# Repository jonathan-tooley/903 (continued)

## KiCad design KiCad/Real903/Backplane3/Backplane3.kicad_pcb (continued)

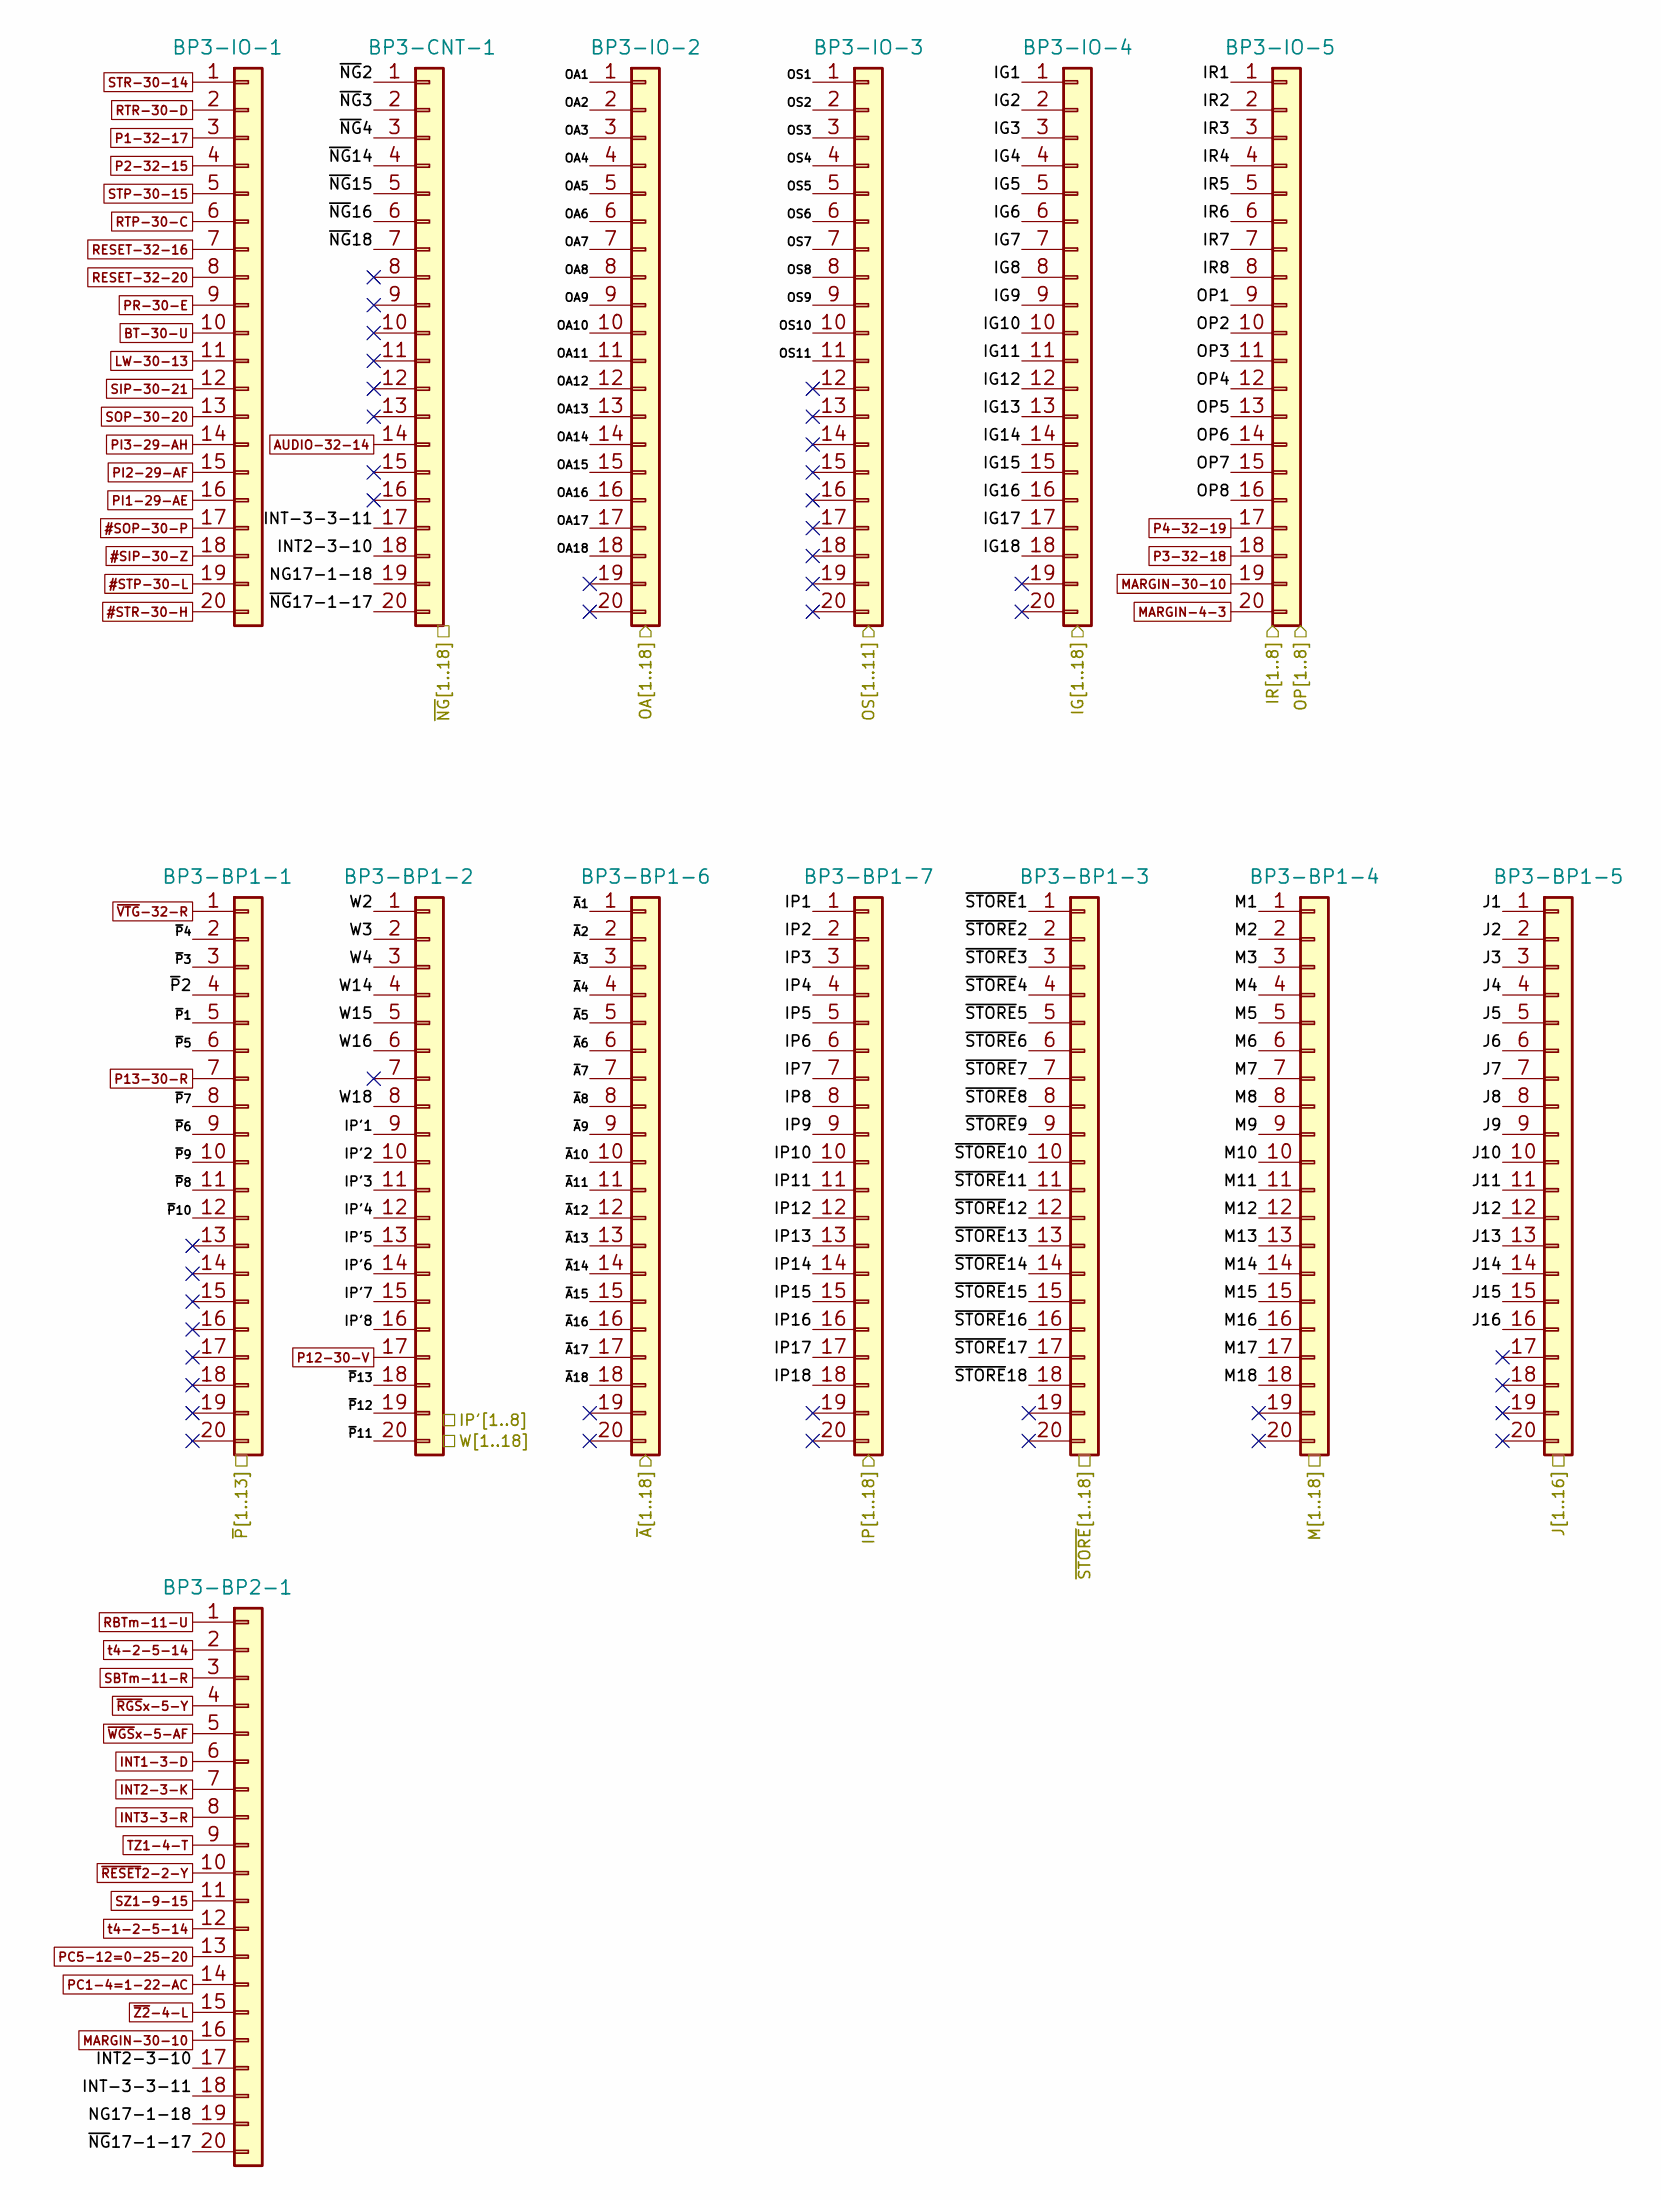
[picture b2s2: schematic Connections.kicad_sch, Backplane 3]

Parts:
BP3-BP1-1, BP3-BP1-2, BP3-BP1-3, BP3-BP1-4, BP3-BP1-5, BP3-BP1-6, BP3-BP1-7, BP3-BP2-1, BP3-CNT-1, BP3-IO-1, BP3-IO-2, BP3-IO-3, BP3-IO-4, BP3-IO-5: IDC-Header_2x10_P2.54mm_Latch_Vertical

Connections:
#SIP-30-Z: BP3-IO-1.18; also elsewhere on the board
#SOP-30-P: BP3-IO-1.17; also elsewhere on the board
#STP-30-L: BP3-IO-1.19; also elsewhere on the board
#STR-30-H: BP3-IO-1.20; also elsewhere on the board
/Connections/IG1: BP3-IO-4.1; also elsewhere on the board
/Connections/IG2: BP3-IO-4.2; also elsewhere on the board
/Connections/IG3: BP3-IO-4.3; also elsewhere on the board
/Connections/IG4: BP3-IO-4.4; also elsewhere on the board
/Connections/IG5: BP3-IO-4.5; also elsewhere on the board
/Connections/IG6: BP3-IO-4.6; also elsewhere on the board
/Connections/IG7: BP3-IO-4.7; also elsewhere on the board
/Connections/IG8: BP3-IO-4.8; also elsewhere on the board
/Connections/IG9: BP3-IO-4.9; also elsewhere on the board
/Connections/IG10: BP3-IO-4.10; also elsewhere on the board
/Connections/IG11: BP3-IO-4.11; also elsewhere on the board
/Connections/IG12: BP3-IO-4.12; also elsewhere on the board
/Connections/IG13: BP3-IO-4.13; also elsewhere on the board
/Connections/IG14: BP3-IO-4.14; also elsewhere on the board
/Connections/IG15: BP3-IO-4.15; also elsewhere on the board
/Connections/IG16: BP3-IO-4.16; also elsewhere on the board
/Connections/IG17: BP3-IO-4.17; also elsewhere on the board
/Connections/IG18: BP3-IO-4.18; also elsewhere on the board
/Connections/INT2-3-10: BP3-BP2-1.17, BP3-CNT-1.18
/Connections/INT-3-3-11: BP3-BP2-1.18, BP3-CNT-1.17
/Connections/IP1: BP3-BP1-7.1; also elsewhere on the board
/Connections/IP2: BP3-BP1-7.2; also elsewhere on the board
/Connections/IP3: BP3-BP1-7.3; also elsewhere on the board
/Connections/IP4: BP3-BP1-7.4; also elsewhere on the board
/Connections/IP5: BP3-BP1-7.5; also elsewhere on the board
/Connections/IP6: BP3-BP1-7.6; also elsewhere on the board
/Connections/IP7: BP3-BP1-7.7; also elsewhere on the board
/Connections/IP8: BP3-BP1-7.8; also elsewhere on the board
/Connections/IP9: BP3-BP1-7.9; also elsewhere on the board
/Connections/IP10: BP3-BP1-7.10; also elsewhere on the board
/Connections/IP11: BP3-BP1-7.11; also elsewhere on the board
/Connections/IP12: BP3-BP1-7.12; also elsewhere on the board
/Connections/IP13: BP3-BP1-7.13; also elsewhere on the board
/Connections/IP14: BP3-BP1-7.14; also elsewhere on the board
/Connections/IP15: BP3-BP1-7.15; also elsewhere on the board
/Connections/IP16: BP3-BP1-7.16; also elsewhere on the board
/Connections/IP17: BP3-BP1-7.17; also elsewhere on the board
/Connections/IP18: BP3-BP1-7.18; also elsewhere on the board
/Connections/IP'1: BP3-BP1-2.9; also elsewhere on the board
/Connections/IP'2: BP3-BP1-2.10; also elsewhere on the board
/Connections/IP'3: BP3-BP1-2.11; also elsewhere on the board
/Connections/IP'4: BP3-BP1-2.12; also elsewhere on the board
/Connections/IP'5: BP3-BP1-2.13; also elsewhere on the board
/Connections/IP'6: BP3-BP1-2.14; also elsewhere on the board
/Connections/IP'7: BP3-BP1-2.15; also elsewhere on the board
/Connections/IP'8: BP3-BP1-2.16; also elsewhere on the board
/Connections/IR1: BP3-IO-5.1; also elsewhere on the board
/Connections/IR2: BP3-IO-5.2; also elsewhere on the board
/Connections/IR3: BP3-IO-5.3; also elsewhere on the board
/Connections/IR4: BP3-IO-5.4; also elsewhere on the board
/Connections/IR5: BP3-IO-5.5; also elsewhere on the board
/Connections/IR6: BP3-IO-5.6; also elsewhere on the board
/Connections/IR7: BP3-IO-5.7; also elsewhere on the board
/Connections/IR8: BP3-IO-5.8; also elsewhere on the board
/Connections/J1: BP3-BP1-5.1; also elsewhere on the board
/Connections/J2: BP3-BP1-5.2; also elsewhere on the board
/Connections/J3: BP3-BP1-5.3; also elsewhere on the board
/Connections/J4: BP3-BP1-5.4; also elsewhere on the board
/Connections/J5: BP3-BP1-5.5; also elsewhere on the board
/Connections/J6: BP3-BP1-5.6; also elsewhere on the board
/Connections/J7: BP3-BP1-5.7; also elsewhere on the board
/Connections/J8: BP3-BP1-5.8; also elsewhere on the board
/Connections/J9: BP3-BP1-5.9; also elsewhere on the board
/Connections/J10: BP3-BP1-5.10; also elsewhere on the board
/Connections/J11: BP3-BP1-5.11; also elsewhere on the board
/Connections/J12: BP3-BP1-5.12; also elsewhere on the board
/Connections/J13: BP3-BP1-5.13; also elsewhere on the board
/Connections/J14: BP3-BP1-5.14; also elsewhere on the board
/Connections/J15: BP3-BP1-5.15; also elsewhere on the board
/Connections/J16: BP3-BP1-5.16; also elsewhere on the board
/Connections/M1: BP3-BP1-4.1; also elsewhere on the board
/Connections/M2: BP3-BP1-4.2; also elsewhere on the board
/Connections/M3: BP3-BP1-4.3; also elsewhere on the board
/Connections/M4: BP3-BP1-4.4; also elsewhere on the board
/Connections/M5: BP3-BP1-4.5; also elsewhere on the board
/Connections/M6: BP3-BP1-4.6; also elsewhere on the board
/Connections/M7: BP3-BP1-4.7; also elsewhere on the board
/Connections/M8: BP3-BP1-4.8; also elsewhere on the board
/Connections/M9: BP3-BP1-4.9; also elsewhere on the board
/Connections/M10: BP3-BP1-4.10; also elsewhere on the board
/Connections/M11: BP3-BP1-4.11; also elsewhere on the board
/Connections/M12: BP3-BP1-4.12; also elsewhere on the board
/Connections/M13: BP3-BP1-4.13; also elsewhere on the board
/Connections/M14: BP3-BP1-4.14; also elsewhere on the board
/Connections/M15: BP3-BP1-4.15; also elsewhere on the board
/Connections/M16: BP3-BP1-4.16; also elsewhere on the board
/Connections/M17: BP3-BP1-4.17; also elsewhere on the board
/Connections/M18: BP3-BP1-4.18; also elsewhere on the board
/Connections/NG17-1-18: BP3-BP2-1.19, BP3-CNT-1.19
/Connections/OA1: BP3-IO-2.1; also elsewhere on the board
/Connections/OA2: BP3-IO-2.2; also elsewhere on the board
/Connections/OA3: BP3-IO-2.3; also elsewhere on the board
/Connections/OA4: BP3-IO-2.4; also elsewhere on the board
/Connections/OA5: BP3-IO-2.5; also elsewhere on the board
/Connections/OA6: BP3-IO-2.6; also elsewhere on the board
/Connections/OA7: BP3-IO-2.7; also elsewhere on the board
/Connections/OA8: BP3-IO-2.8; also elsewhere on the board
/Connections/OA9: BP3-IO-2.9; also elsewhere on the board
/Connections/OA10: BP3-IO-2.10; also elsewhere on the board
/Connections/OA11: BP3-IO-2.11; also elsewhere on the board
/Connections/OA12: BP3-IO-2.12; also elsewhere on the board
/Connections/OA13: BP3-IO-2.13; also elsewhere on the board
/Connections/OA14: BP3-IO-2.14; also elsewhere on the board
/Connections/OA15: BP3-IO-2.15; also elsewhere on the board
/Connections/OA16: BP3-IO-2.16; also elsewhere on the board
/Connections/OA17: BP3-IO-2.17; also elsewhere on the board
/Connections/OA18: BP3-IO-2.18; also elsewhere on the board
/Connections/OP1: BP3-IO-5.9; also elsewhere on the board
/Connections/OP2: BP3-IO-5.10; also elsewhere on the board
/Connections/OP3: BP3-IO-5.11; also elsewhere on the board
/Connections/OP4: BP3-IO-5.12; also elsewhere on the board
/Connections/OP5: BP3-IO-5.13; also elsewhere on the board
/Connections/OP6: BP3-IO-5.14; also elsewhere on the board
/Connections/OP7: BP3-IO-5.15; also elsewhere on the board
/Connections/OP8: BP3-IO-5.16; also elsewhere on the board
/Connections/OS1: BP3-IO-3.1; also elsewhere on the board
/Connections/OS2: BP3-IO-3.2; also elsewhere on the board
/Connections/OS3: BP3-IO-3.3; also elsewhere on the board
/Connections/OS4: BP3-IO-3.4; also elsewhere on the board
/Connections/OS5: BP3-IO-3.5; also elsewhere on the board
/Connections/OS6: BP3-IO-3.6; also elsewhere on the board
/Connections/OS7: BP3-IO-3.7; also elsewhere on the board
/Connections/OS8: BP3-IO-3.8; also elsewhere on the board
/Connections/OS9: BP3-IO-3.9; also elsewhere on the board
/Connections/OS10: BP3-IO-3.10; also elsewhere on the board
/Connections/OS11: BP3-IO-3.11; also elsewhere on the board
/Connections/W2: BP3-BP1-2.1; also elsewhere on the board
/Connections/W3: BP3-BP1-2.2; also elsewhere on the board
/Connections/W4: BP3-BP1-2.3; also elsewhere on the board
/Connections/W14: BP3-BP1-2.4; also elsewhere on the board
/Connections/W15: BP3-BP1-2.5; also elsewhere on the board
/Connections/W16: BP3-BP1-2.6; also elsewhere on the board
/Connections/W18: BP3-BP1-2.8; also elsewhere on the board
/Connections/~A1: BP3-BP1-6.1; also elsewhere on the board
/Connections/~A2: BP3-BP1-6.2; also elsewhere on the board
/Connections/~A3: BP3-BP1-6.3; also elsewhere on the board
/Connections/~A4: BP3-BP1-6.4; also elsewhere on the board
/Connections/~A5: BP3-BP1-6.5; also elsewhere on the board
/Connections/~A6: BP3-BP1-6.6; also elsewhere on the board
/Connections/~A7: BP3-BP1-6.7; also elsewhere on the board
/Connections/~A8: BP3-BP1-6.8; also elsewhere on the board
/Connections/~A9: BP3-BP1-6.9; also elsewhere on the board
/Connections/~A10: BP3-BP1-6.10; also elsewhere on the board
/Connections/~A11: BP3-BP1-6.11; also elsewhere on the board
/Connections/~A12: BP3-BP1-6.12; also elsewhere on the board
/Connections/~A13: BP3-BP1-6.13; also elsewhere on the board
/Connections/~A14: BP3-BP1-6.14; also elsewhere on the board
/Connections/~A15: BP3-BP1-6.15; also elsewhere on the board
/Connections/~A16: BP3-BP1-6.16; also elsewhere on the board
/Connections/~A17: BP3-BP1-6.17; also elsewhere on the board
/Connections/~A18: BP3-BP1-6.18; also elsewhere on the board
/Connections/~NG2: BP3-CNT-1.1; also elsewhere on the board
/Connections/~NG3: BP3-CNT-1.2; also elsewhere on the board
/Connections/~NG4: BP3-CNT-1.3; also elsewhere on the board
/Connections/~NG14: BP3-CNT-1.4; also elsewhere on the board
/Connections/~NG15: BP3-CNT-1.5; also elsewhere on the board
/Connections/~NG16: BP3-CNT-1.6; also elsewhere on the board
/Connections/~NG17-1-17: BP3-BP2-1.20, BP3-CNT-1.20
/Connections/~NG18: BP3-CNT-1.7; also elsewhere on the board
/Connections/~P1: BP3-BP1-1.5; also elsewhere on the board
/Connections/~P2: BP3-BP1-1.4; also elsewhere on the board
/Connections/~P3: BP3-BP1-1.3; also elsewhere on the board
/Connections/~P4: BP3-BP1-1.2; also elsewhere on the board
/Connections/~P5: BP3-BP1-1.6; also elsewhere on the board
/Connections/~P6: BP3-BP1-1.9; also elsewhere on the board
/Connections/~P7: BP3-BP1-1.8; also elsewhere on the board
/Connections/~P8: BP3-BP1-1.11; also elsewhere on the board
/Connections/~P9: BP3-BP1-1.10; also elsewhere on the board
/Connections/~P10: BP3-BP1-1.12; also elsewhere on the board
/Connections/~P11: BP3-BP1-2.20; also elsewhere on the board
/Connections/~P12: BP3-BP1-2.19; also elsewhere on the board
/Connections/~P13: BP3-BP1-2.18; also elsewhere on the board
/Connections/~STORE1: BP3-BP1-3.1; also elsewhere on the board
/Connections/~STORE2: BP3-BP1-3.2; also elsewhere on the board
/Connections/~STORE3: BP3-BP1-3.3; also elsewhere on the board
/Connections/~STORE4: BP3-BP1-3.4; also elsewhere on the board
/Connections/~STORE5: BP3-BP1-3.5; also elsewhere on the board
/Connections/~STORE6: BP3-BP1-3.6; also elsewhere on the board
/Connections/~STORE7: BP3-BP1-3.7; also elsewhere on the board
/Connections/~STORE8: BP3-BP1-3.8; also elsewhere on the board
/Connections/~STORE9: BP3-BP1-3.9; also elsewhere on the board
/Connections/~STORE10: BP3-BP1-3.10; also elsewhere on the board
/Connections/~STORE11: BP3-BP1-3.11; also elsewhere on the board
/Connections/~STORE12: BP3-BP1-3.12; also elsewhere on the board
/Connections/~STORE13: BP3-BP1-3.13; also elsewhere on the board
/Connections/~STORE14: BP3-BP1-3.14; also elsewhere on the board
/Connections/~STORE15: BP3-BP1-3.15; also elsewhere on the board
/Connections/~STORE16: BP3-BP1-3.16; also elsewhere on the board
/Connections/~STORE17: BP3-BP1-3.17; also elsewhere on the board
/Connections/~STORE18: BP3-BP1-3.18; also elsewhere on the board
AUDIO-32-14: BP3-CNT-1.14; also elsewhere on the board
BT-30-U: BP3-IO-1.10; also elsewhere on the board
INT1-3-D: BP3-BP2-1.6; also elsewhere on the board
INT2-3-K: BP3-BP2-1.7; also elsewhere on the board
INT3-3-R: BP3-BP2-1.8; also elsewhere on the board
LW-30-13: BP3-IO-1.11; also elsewhere on the board
MARGIN-4-3: BP3-IO-5.20
MARGIN-30-10: BP3-BP2-1.16, BP3-IO-5.19; also elsewhere on the board
P1-32-17: BP3-IO-1.3; also elsewhere on the board
P2-32-15: BP3-IO-1.4; also elsewhere on the board
P3-32-18: BP3-IO-5.18; also elsewhere on the board
P4-32-19: BP3-IO-5.17; also elsewhere on the board
P12-30-V: BP3-BP1-2.17; also elsewhere on the board
P13-30-R: BP3-BP1-1.7; also elsewhere on the board
PC1-4=1-22-AC: BP3-BP2-1.14; also elsewhere on the board
PC5-12=0-25-20: BP3-BP2-1.13; also elsewhere on the board
PI1-29-AE: BP3-IO-1.16; also elsewhere on the board
PI2-29-AF: BP3-IO-1.15; also elsewhere on the board
PI3-29-AH: BP3-IO-1.14; also elsewhere on the board
PR-30-E: BP3-IO-1.9; also elsewhere on the board
RBTm-11-U: BP3-BP2-1.1; also elsewhere on the board
RESET-32-16: BP3-IO-1.7; also elsewhere on the board
RESET-32-20: BP3-IO-1.8; also elsewhere on the board
RTP-30-C: BP3-IO-1.6; also elsewhere on the board
RTR-30-D: BP3-IO-1.2; also elsewhere on the board
SBTm-11-R: BP3-BP2-1.3; also elsewhere on the board
SIP-30-21: BP3-IO-1.12; also elsewhere on the board
SOP-30-20: BP3-IO-1.13; also elsewhere on the board
STP-30-15: BP3-IO-1.5; also elsewhere on the board
STR-30-14: BP3-IO-1.1; also elsewhere on the board
SZ1-9-15: BP3-BP2-1.11; also elsewhere on the board
TZ1-4-T: BP3-BP2-1.9; also elsewhere on the board
t4-2-5-14: BP3-BP2-1.2, BP3-BP2-1.12; also elsewhere on the board
~RESET2-2-Y: BP3-BP2-1.10; also elsewhere on the board
~RGSx-5-Y: BP3-BP2-1.4; also elsewhere on the board
~VTG-32-R: BP3-BP1-1.1; also elsewhere on the board
~WGSx-5-AF: BP3-BP2-1.5; also elsewhere on the board
~Z2-4-L: BP3-BP2-1.15; also elsewhere on the board

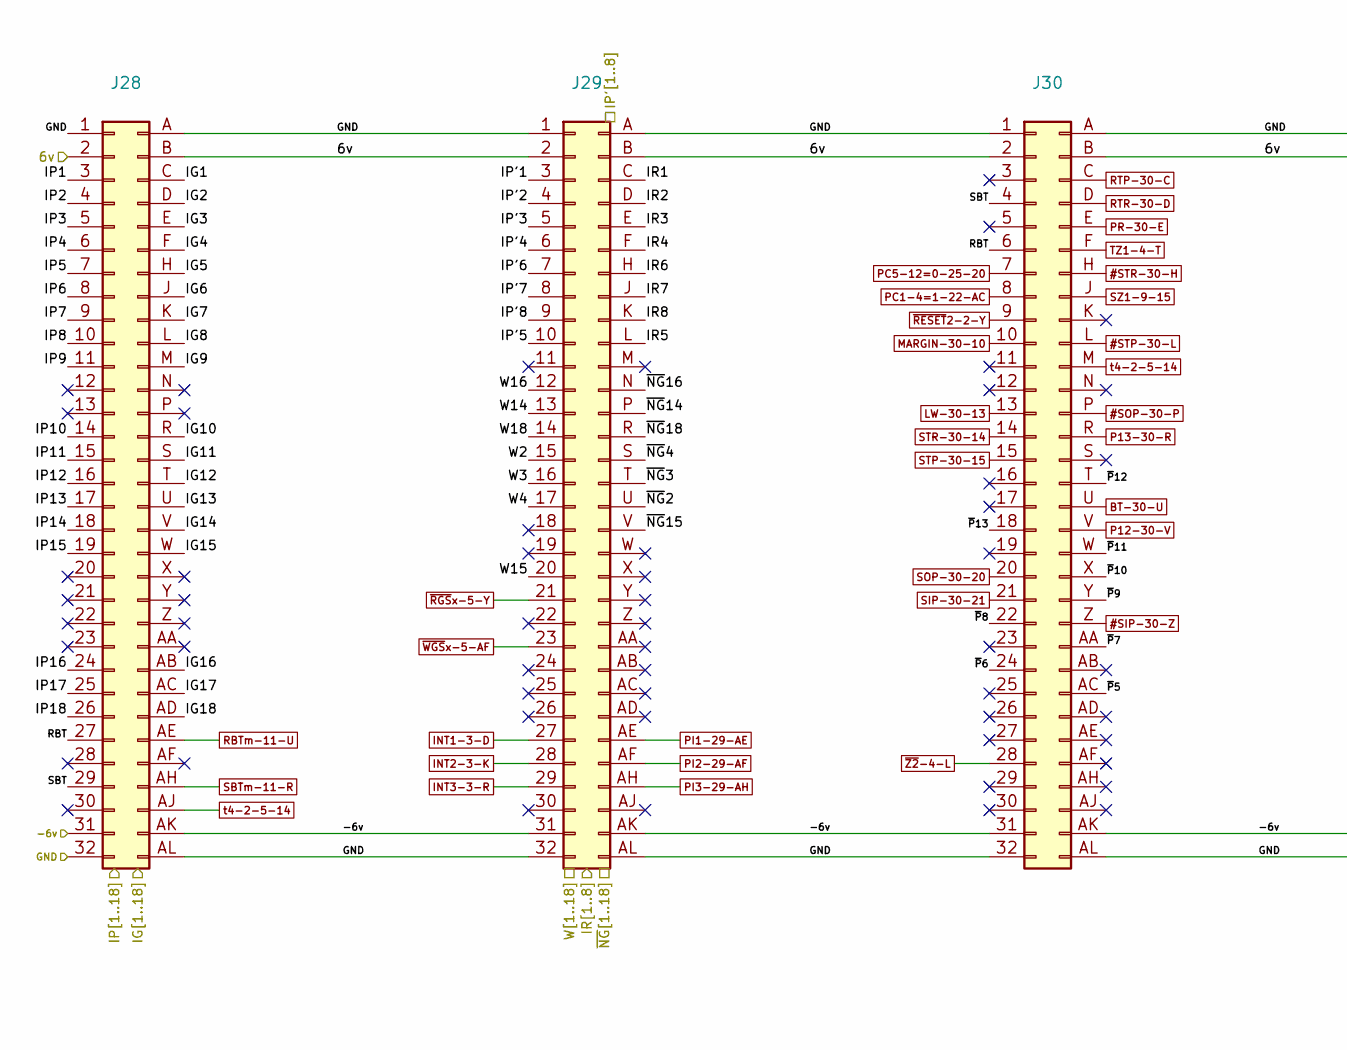
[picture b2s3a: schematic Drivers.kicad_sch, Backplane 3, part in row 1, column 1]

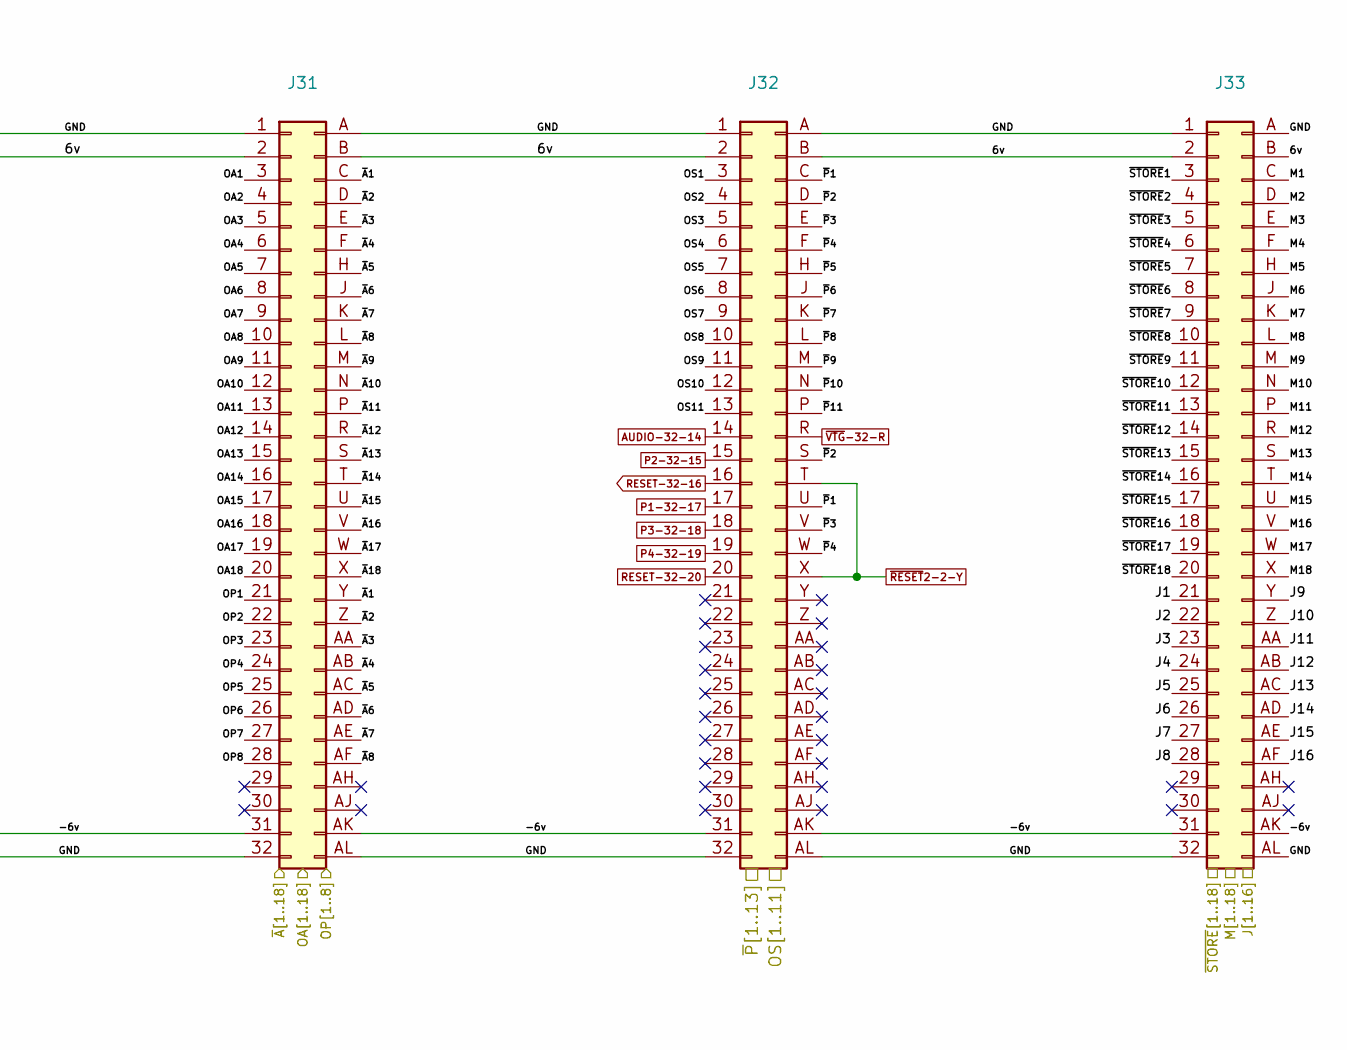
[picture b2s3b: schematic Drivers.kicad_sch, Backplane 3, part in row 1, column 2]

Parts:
J28, J29, J30, J31, J32, J33: DIN41612_B_2x32_Vertical

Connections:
6v: J28.2, J28.B, J29.2, J29.B, J30.2, J30.B, J31.2, J31.B, J32.2, J32.B, J33.2, J33.B; also elsewhere on the board
#SIP-30-Z: J30.Z; also elsewhere on the board
#SOP-30-P: J30.P; also elsewhere on the board
#STP-30-L: J30.L; also elsewhere on the board
#STR-30-H: J30.H; also elsewhere on the board
/Connections/IG1: J28.C; also elsewhere on the board
/Connections/IG2: J28.D; also elsewhere on the board
/Connections/IG3: J28.E; also elsewhere on the board
/Connections/IG4: J28.F; also elsewhere on the board
/Connections/IG5: J28.H; also elsewhere on the board
/Connections/IG6: J28.J; also elsewhere on the board
/Connections/IG7: J28.K; also elsewhere on the board
/Connections/IG8: J28.L; also elsewhere on the board
/Connections/IG9: J28.M; also elsewhere on the board
/Connections/IG10: J28.R; also elsewhere on the board
/Connections/IG11: J28.S; also elsewhere on the board
/Connections/IG12: J28.T; also elsewhere on the board
/Connections/IG13: J28.U; also elsewhere on the board
/Connections/IG14: J28.V; also elsewhere on the board
/Connections/IG15: J28.W; also elsewhere on the board
/Connections/IG16: J28.AB; also elsewhere on the board
/Connections/IG17: J28.AC; also elsewhere on the board
/Connections/IG18: J28.AD; also elsewhere on the board
/Connections/IP1: J28.3; also elsewhere on the board
/Connections/IP2: J28.4; also elsewhere on the board
/Connections/IP3: J28.5; also elsewhere on the board
/Connections/IP4: J28.6; also elsewhere on the board
/Connections/IP5: J28.7; also elsewhere on the board
/Connections/IP6: J28.8; also elsewhere on the board
/Connections/IP7: J28.9; also elsewhere on the board
/Connections/IP8: J28.10; also elsewhere on the board
/Connections/IP9: J28.11; also elsewhere on the board
/Connections/IP10: J28.14; also elsewhere on the board
/Connections/IP11: J28.15; also elsewhere on the board
/Connections/IP12: J28.16; also elsewhere on the board
/Connections/IP13: J28.17; also elsewhere on the board
/Connections/IP14: J28.18; also elsewhere on the board
/Connections/IP15: J28.19; also elsewhere on the board
/Connections/IP16: J28.24; also elsewhere on the board
/Connections/IP17: J28.25; also elsewhere on the board
/Connections/IP18: J28.26; also elsewhere on the board
/Connections/IP'1: J29.3; also elsewhere on the board
/Connections/IP'2: J29.4; also elsewhere on the board
/Connections/IP'3: J29.5; also elsewhere on the board
/Connections/IP'4: J29.6; also elsewhere on the board
/Connections/IP'5: J29.10; also elsewhere on the board
/Connections/IP'6: J29.7; also elsewhere on the board
/Connections/IP'7: J29.8; also elsewhere on the board
/Connections/IP'8: J29.9; also elsewhere on the board
/Connections/IR1: J29.C; also elsewhere on the board
/Connections/IR2: J29.D; also elsewhere on the board
/Connections/IR3: J29.E; also elsewhere on the board
/Connections/IR4: J29.F; also elsewhere on the board
/Connections/IR5: J29.L; also elsewhere on the board
/Connections/IR6: J29.H; also elsewhere on the board
/Connections/IR7: J29.J; also elsewhere on the board
/Connections/IR8: J29.K; also elsewhere on the board
/Connections/J1: J33.21; also elsewhere on the board
/Connections/J2: J33.22; also elsewhere on the board
/Connections/J3: J33.23; also elsewhere on the board
/Connections/J4: J33.24; also elsewhere on the board
/Connections/J5: J33.25; also elsewhere on the board
/Connections/J6: J33.26; also elsewhere on the board
/Connections/J7: J33.27; also elsewhere on the board
/Connections/J8: J33.28; also elsewhere on the board
/Connections/J9: J33.Y; also elsewhere on the board
/Connections/J10: J33.Z; also elsewhere on the board
/Connections/J11: J33.AA; also elsewhere on the board
/Connections/J12: J33.AB; also elsewhere on the board
/Connections/J13: J33.AC; also elsewhere on the board
/Connections/J14: J33.AD; also elsewhere on the board
/Connections/J15: J33.AE; also elsewhere on the board
/Connections/J16: J33.AF; also elsewhere on the board
/Connections/M1: J33.C; also elsewhere on the board
/Connections/M2: J33.D; also elsewhere on the board
/Connections/M3: J33.E; also elsewhere on the board
/Connections/M4: J33.F; also elsewhere on the board
/Connections/M5: J33.H; also elsewhere on the board
/Connections/M6: J33.J; also elsewhere on the board
/Connections/M7: J33.K; also elsewhere on the board
/Connections/M8: J33.L; also elsewhere on the board
/Connections/M9: J33.M; also elsewhere on the board
/Connections/M10: J33.N; also elsewhere on the board
/Connections/M11: J33.P; also elsewhere on the board
/Connections/M12: J33.R; also elsewhere on the board
/Connections/M13: J33.S; also elsewhere on the board
/Connections/M14: J33.T; also elsewhere on the board
/Connections/M15: J33.U; also elsewhere on the board
/Connections/M16: J33.V; also elsewhere on the board
/Connections/M17: J33.W; also elsewhere on the board
/Connections/M18: J33.X; also elsewhere on the board
/Connections/OA1: J31.3; also elsewhere on the board
/Connections/OA2: J31.4; also elsewhere on the board
/Connections/OA3: J31.5; also elsewhere on the board
/Connections/OA4: J31.6; also elsewhere on the board
/Connections/OA5: J31.7; also elsewhere on the board
/Connections/OA6: J31.8; also elsewhere on the board
/Connections/OA7: J31.9; also elsewhere on the board
/Connections/OA8: J31.10; also elsewhere on the board
/Connections/OA9: J31.11; also elsewhere on the board
/Connections/OA10: J31.12; also elsewhere on the board
/Connections/OA11: J31.13; also elsewhere on the board
/Connections/OA12: J31.14; also elsewhere on the board
/Connections/OA13: J31.15; also elsewhere on the board
/Connections/OA14: J31.16; also elsewhere on the board
/Connections/OA15: J31.17; also elsewhere on the board
/Connections/OA16: J31.18; also elsewhere on the board
/Connections/OA17: J31.19; also elsewhere on the board
/Connections/OA18: J31.20; also elsewhere on the board
/Connections/OP1: J31.21; also elsewhere on the board
/Connections/OP2: J31.22; also elsewhere on the board
/Connections/OP3: J31.23; also elsewhere on the board
/Connections/OP4: J31.24; also elsewhere on the board
/Connections/OP5: J31.25; also elsewhere on the board
/Connections/OP6: J31.26; also elsewhere on the board
/Connections/OP7: J31.27; also elsewhere on the board
/Connections/OP8: J31.28; also elsewhere on the board
/Connections/OS1: J32.3; also elsewhere on the board
/Connections/OS2: J32.4; also elsewhere on the board
/Connections/OS3: J32.5; also elsewhere on the board
/Connections/OS4: J32.6; also elsewhere on the board
/Connections/OS5: J32.7; also elsewhere on the board
/Connections/OS6: J32.8; also elsewhere on the board
/Connections/OS7: J32.9; also elsewhere on the board
/Connections/OS8: J32.10; also elsewhere on the board
/Connections/OS9: J32.11; also elsewhere on the board
/Connections/OS10: J32.12; also elsewhere on the board
/Connections/OS11: J32.13; also elsewhere on the board
/Connections/W2: J29.15; also elsewhere on the board
/Connections/W3: J29.16; also elsewhere on the board
/Connections/W4: J29.17; also elsewhere on the board
/Connections/W14: J29.13; also elsewhere on the board
/Connections/W15: J29.20; also elsewhere on the board
/Connections/W16: J29.12; also elsewhere on the board
/Connections/W18: J29.14; also elsewhere on the board
/Connections/~A1: J31.C, J31.Y; also elsewhere on the board
/Connections/~A2: J31.D, J31.Z; also elsewhere on the board
/Connections/~A3: J31.AA, J31.E; also elsewhere on the board
/Connections/~A4: J31.AB, J31.F; also elsewhere on the board
/Connections/~A5: J31.AC, J31.H; also elsewhere on the board
/Connections/~A6: J31.AD, J31.J; also elsewhere on the board
/Connections/~A7: J31.AE, J31.K; also elsewhere on the board
/Connections/~A8: J31.AF, J31.L; also elsewhere on the board
/Connections/~A9: J31.M; also elsewhere on the board
/Connections/~A10: J31.N; also elsewhere on the board
/Connections/~A11: J31.P; also elsewhere on the board
/Connections/~A12: J31.R; also elsewhere on the board
/Connections/~A13: J31.S; also elsewhere on the board
/Connections/~A14: J31.T; also elsewhere on the board
/Connections/~A15: J31.U; also elsewhere on the board
/Connections/~A16: J31.V; also elsewhere on the board
/Connections/~A17: J31.W; also elsewhere on the board
/Connections/~A18: J31.X; also elsewhere on the board
/Connections/~NG2: J29.U; also elsewhere on the board
/Connections/~NG3: J29.T; also elsewhere on the board
/Connections/~NG4: J29.S; also elsewhere on the board
/Connections/~NG14: J29.P; also elsewhere on the board
/Connections/~NG15: J29.V; also elsewhere on the board
/Connections/~NG16: J29.N; also elsewhere on the board
/Connections/~NG18: J29.R; also elsewhere on the board
/Connections/~P1: J32.C, J32.U; also elsewhere on the board
/Connections/~P2: J32.D, J32.S; also elsewhere on the board
/Connections/~P3: J32.E, J32.V; also elsewhere on the board
/Connections/~P4: J32.F, J32.W; also elsewhere on the board
/Connections/~P5: J30.AC, J32.H; also elsewhere on the board
/Connections/~P6: J30.24, J32.J; also elsewhere on the board
/Connections/~P7: J30.AA, J32.K; also elsewhere on the board
/Connections/~P8: J30.22, J32.L; also elsewhere on the board
/Connections/~P9: J30.Y, J32.M; also elsewhere on the board
/Connections/~P10: J30.X, J32.N; also elsewhere on the board
/Connections/~P11: J30.W, J32.P; also elsewhere on the board
/Connections/~P12: J30.T; also elsewhere on the board
/Connections/~P13: J30.18; also elsewhere on the board
/Connections/~STORE1: J33.3; also elsewhere on the board
/Connections/~STORE2: J33.4; also elsewhere on the board
/Connections/~STORE3: J33.5; also elsewhere on the board
/Connections/~STORE4: J33.6; also elsewhere on the board
/Connections/~STORE5: J33.7; also elsewhere on the board
/Connections/~STORE6: J33.8; also elsewhere on the board
/Connections/~STORE7: J33.9; also elsewhere on the board
/Connections/~STORE8: J33.10; also elsewhere on the board
/Connections/~STORE9: J33.11; also elsewhere on the board
/Connections/~STORE10: J33.12; also elsewhere on the board
/Connections/~STORE11: J33.13; also elsewhere on the board
/Connections/~STORE12: J33.14; also elsewhere on the board
/Connections/~STORE13: J33.15; also elsewhere on the board
/Connections/~STORE14: J33.16; also elsewhere on the board
/Connections/~STORE15: J33.17; also elsewhere on the board
/Connections/~STORE16: J33.18; also elsewhere on the board
/Connections/~STORE17: J33.19; also elsewhere on the board
/Connections/~STORE18: J33.20; also elsewhere on the board
/Drivers/RBT: J28.27, J30.6
/Drivers/SBT: J28.29, J30.4
AUDIO-32-14: J32.14; also elsewhere on the board
BT-30-U: J30.U; also elsewhere on the board
GND: J28.1, J28.32, J28.A, J28.AL, J29.1, J29.32, J29.A, J29.AL, J30.1, J30.32, J30.A, J30.AL, J31.1, J31.32, J31.A, J31.AL, J32.1, J32.32, J32.A, J32.AL, J33.1, J33.32, J33.A, J33.AL; also elsewhere on the board
INT1-3-D: J29.27; also elsewhere on the board
INT2-3-K: J29.28; also elsewhere on the board
INT3-3-R: J29.29; also elsewhere on the board
LW-30-13: J30.13; also elsewhere on the board
MARGIN-30-10: J30.10; also elsewhere on the board
Neg6v: J28.31, J28.AK, J29.31, J29.AK, J30.31, J30.AK, J31.31, J31.AK, J32.31, J32.AK, J33.31, J33.AK; also elsewhere on the board
P1-32-17: J32.17; also elsewhere on the board
P2-32-15: J32.15; also elsewhere on the board
P3-32-18: J32.18; also elsewhere on the board
P4-32-19: J32.19; also elsewhere on the board
P12-30-V: J30.V; also elsewhere on the board
P13-30-R: J30.R; also elsewhere on the board
PC1-4=1-22-AC: J30.8; also elsewhere on the board
PC5-12=0-25-20: J30.7; also elsewhere on the board
PI1-29-AE: J29.AE; also elsewhere on the board
PI2-29-AF: J29.AF; also elsewhere on the board
PI3-29-AH: J29.AH; also elsewhere on the board
PR-30-E: J30.E; also elsewhere on the board
RBTm-11-U: J28.AE; also elsewhere on the board
RESET-32-16: J32.16; also elsewhere on the board
RESET-32-20: J32.20; also elsewhere on the board
RTP-30-C: J30.C; also elsewhere on the board
RTR-30-D: J30.D; also elsewhere on the board
SBTm-11-R: J28.AH; also elsewhere on the board
SIP-30-21: J30.21; also elsewhere on the board
SOP-30-20: J30.20; also elsewhere on the board
STP-30-15: J30.15; also elsewhere on the board
STR-30-14: J30.14; also elsewhere on the board
SZ1-9-15: J30.J; also elsewhere on the board
TZ1-4-T: J30.F; also elsewhere on the board
t4-2-5-14: J28.AJ, J30.M; also elsewhere on the board
~RESET2-2-Y: J30.9, J32.T, J32.X; also elsewhere on the board
~RGSx-5-Y: J29.21; also elsewhere on the board
~VTG-32-R: J32.R; also elsewhere on the board
~WGSx-5-AF: J29.23; also elsewhere on the board
~Z2-4-L: J30.28; also elsewhere on the board
